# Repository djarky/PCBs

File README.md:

# PCBs
Various PCBs

- game controller based on digispark
- clap switch with relay
- amps?
- others

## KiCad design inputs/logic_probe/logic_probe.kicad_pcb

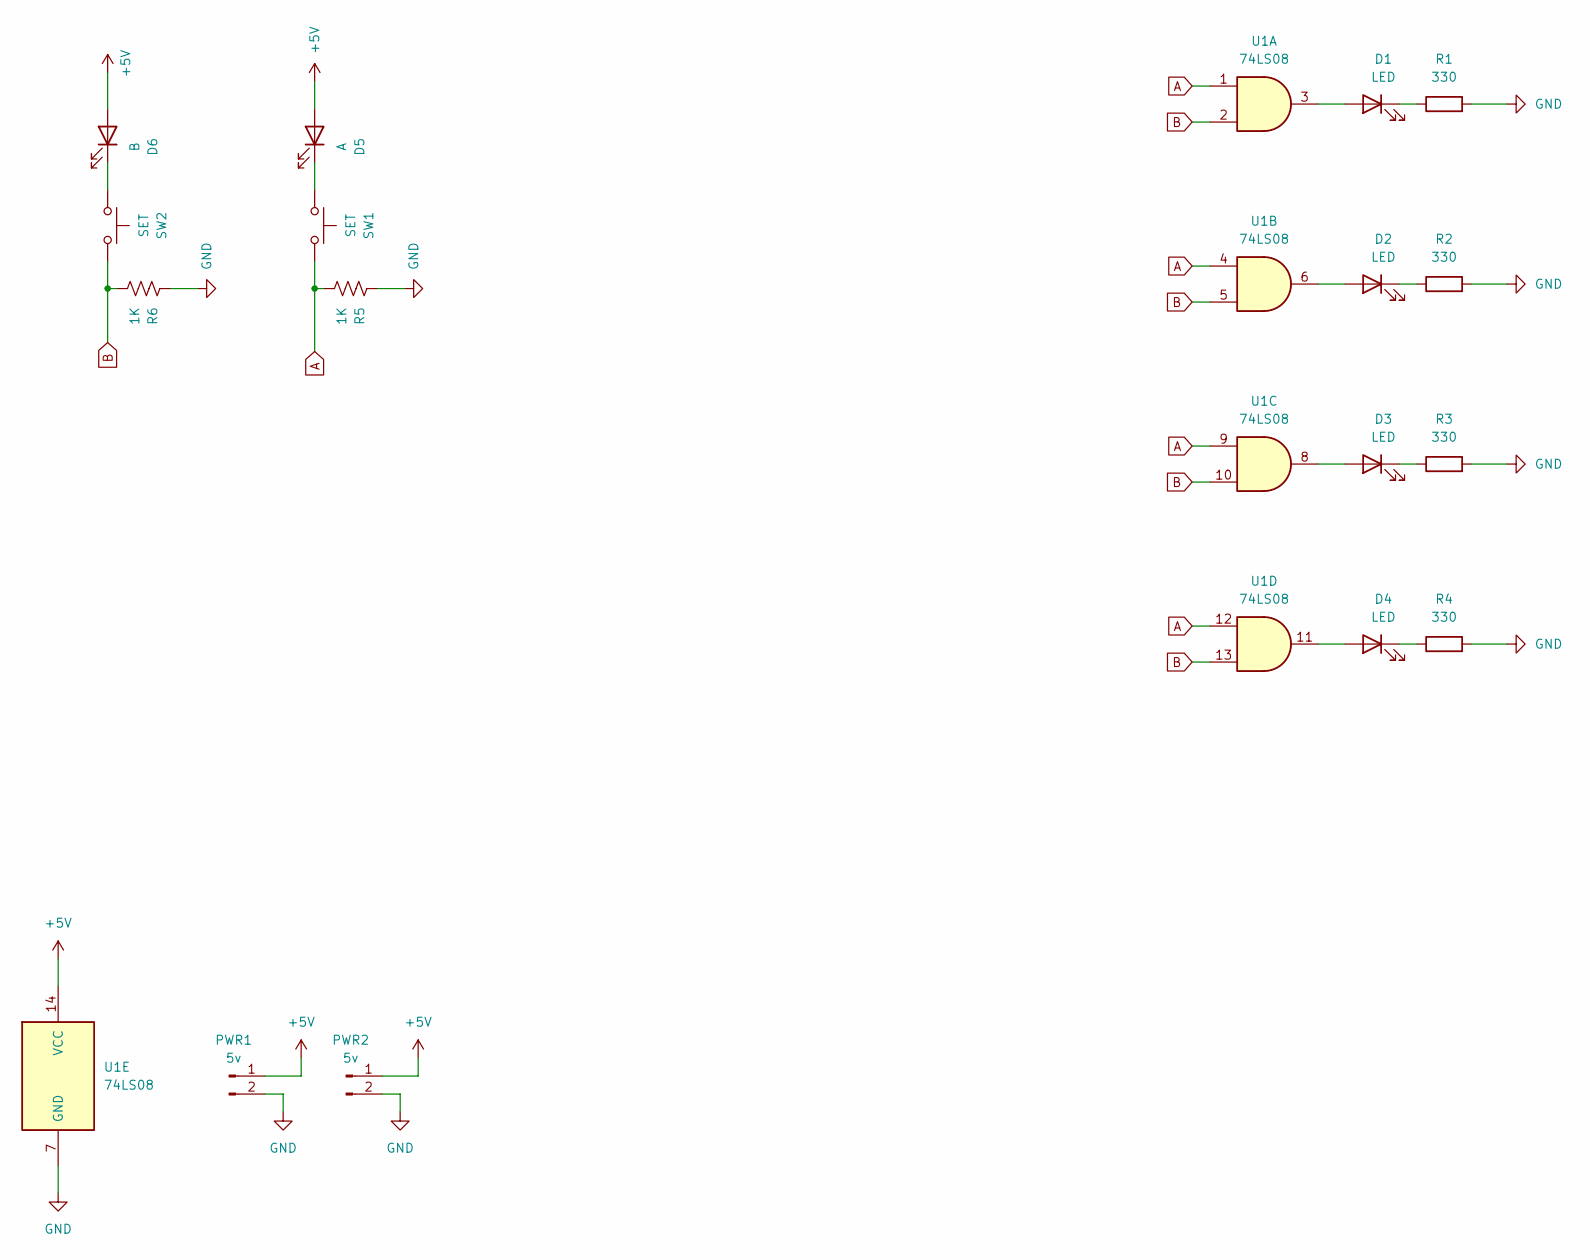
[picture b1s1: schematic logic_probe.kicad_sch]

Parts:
D1, D2, D3, D4: LED; LED_D4.0mm
D5: A; LED_D4.0mm
D6: B; LED_D4.0mm
PWR1, PWR2: 5v; PinSocket_1x02_P2.54mm_Vertical
R1, R2, R3, R4: 330; R_Axial_DIN0309_L9.0mm_D3.2mm_P12.70mm_Horizontal
R5, R6: 1K; R_Axial_DIN0309_L9.0mm_D3.2mm_P12.70mm_Horizontal
SW1, SW2: SET; SW_PUSH-12mm_Wuerth-430476085716
U1: 74LS08; DIP-14_W7.62mm_Socket_LongPads

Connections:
+5V: D5.2 (A), D6.2 (A), PWR1.1, PWR2.1, U1.14 (VCC)
A: R5.2, SW1.2, U1.1, U1.4, U1.9, U1.12
B: R6.2, SW2.2, U1.2, U1.5, U1.10, U1.13
GND: PWR1.2, PWR2.2, R1.2, R2.2, R3.2, R4.2, R5.1, R6.1, U1.7 (GND)
unnamed: D1.2 (A), U1.3
unnamed: D1.1 (K), R1.1
unnamed: D2.2 (A), U1.6
unnamed: D2.1 (K), R2.1
unnamed: D3.2 (A), U1.8
unnamed: D3.1 (K), R3.1
unnamed: D4.2 (A), U1.11
unnamed: D4.1 (K), R4.1
unnamed: D5.1 (K), SW1.1
unnamed: D6.1 (K), SW2.1

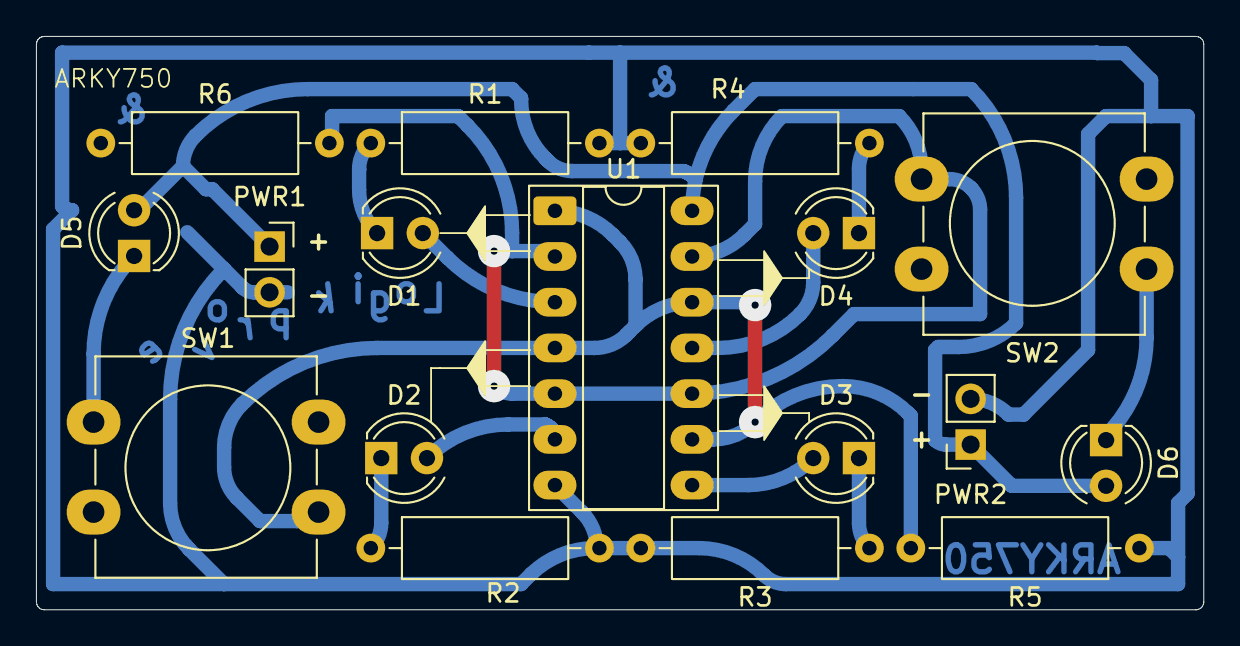
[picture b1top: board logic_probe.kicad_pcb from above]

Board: 2 copper layers, 64.8 x 31.8 mm, 17 parts (0 on the bottom side), 14 nets.

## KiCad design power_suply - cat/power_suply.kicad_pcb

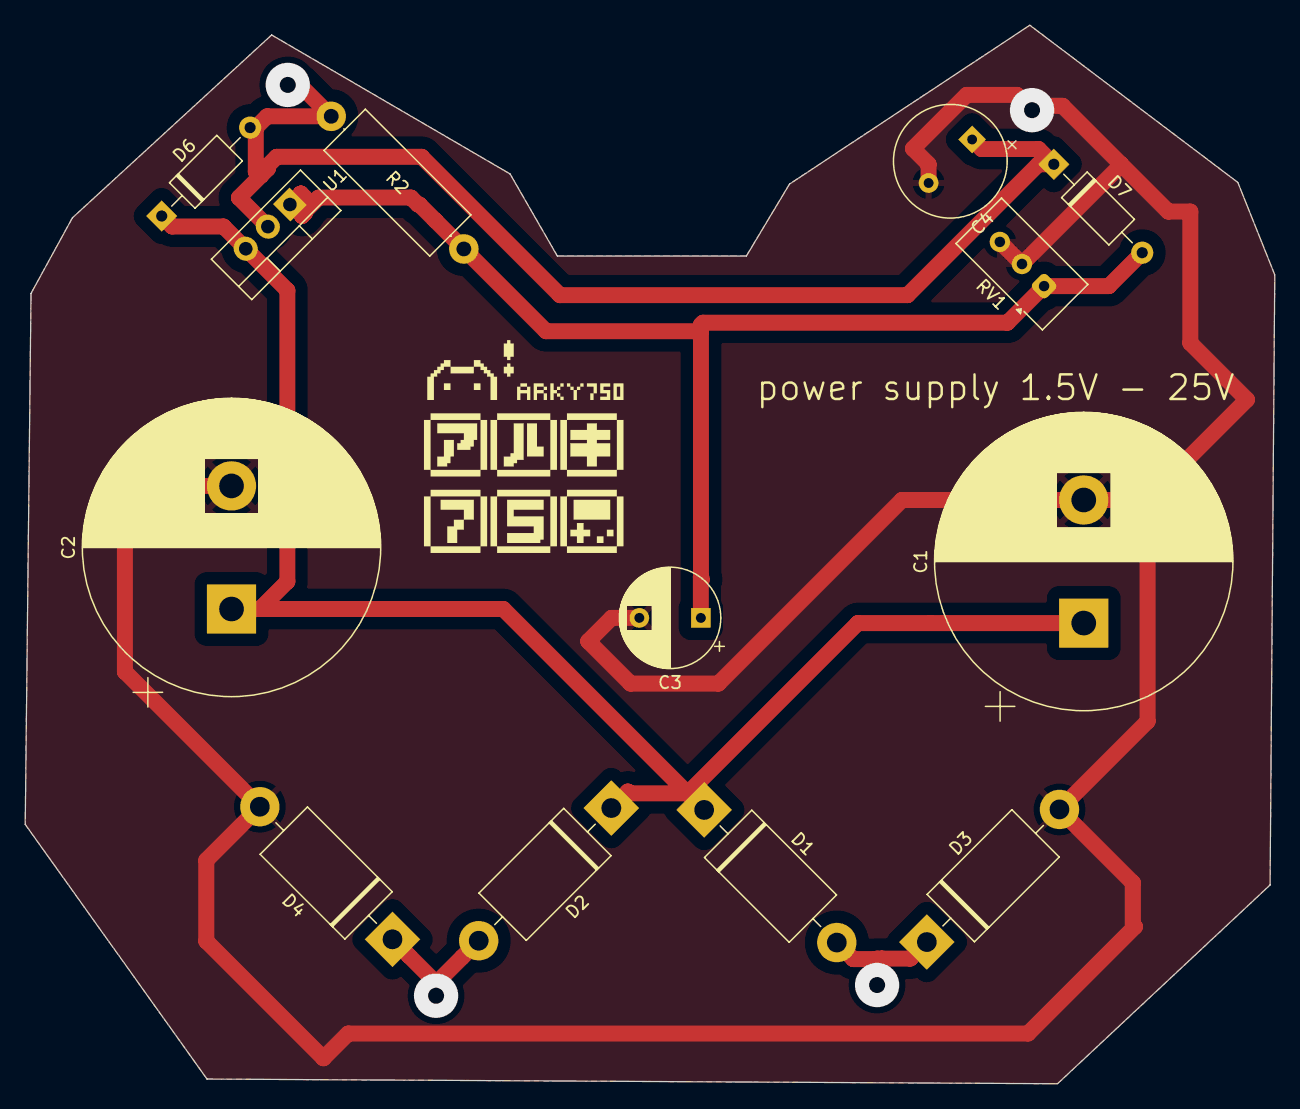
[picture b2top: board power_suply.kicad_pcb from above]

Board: 2 copper layers, 101.5 x 86.0 mm, 13 parts (0 on the bottom side), 6 nets.

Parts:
C1, C2: 2200uF 50v; CP_Radial_D24.0mm_P10.00mm_SnapIn
C3: 33uF 10V; CP_Radial_D8.0mm_P5.00mm
C4: 1uF 25V tantalio; CP_Radial_Tantal_D9.0mm_P5.00mm
D1, D2, D3, D4: D_Filled; D_DO-201AD_P15.24mm_Horizontal
D6: D_Filled; D_A-405_P10.16mm_Horizontal
D7: 1N4004; D_A-405_P10.16mm_Horizontal
R2: 240; R_Axial_DIN0414_L11.9mm_D4.5mm_P15.24mm_Horizontal
RV1: 5K; Potentiometer_Vishay_T93YA_Vertical
U1: LM317_TO-220; TO-220-3_Vertical

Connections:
GND: C1.2, C2.2, C3.2, C4.2, D3.2 (A), D4.2 (A), RV1.2, RV1.3
unnamed: D2.2 (A), D4.1 (K)
unnamed: C3.1, D7.2 (A), R2.2, RV1.1, U1.1 (ADJ)
T1: D1.2 (A), D3.1 (K)
Vin: C1.1, C2.1, D1.1 (K), D2.1 (K), D6.1 (K), U1.3 (VI)
Vout: C4.1, D6.2 (A), D7.1 (K), R2.1, U1.2 (VO)

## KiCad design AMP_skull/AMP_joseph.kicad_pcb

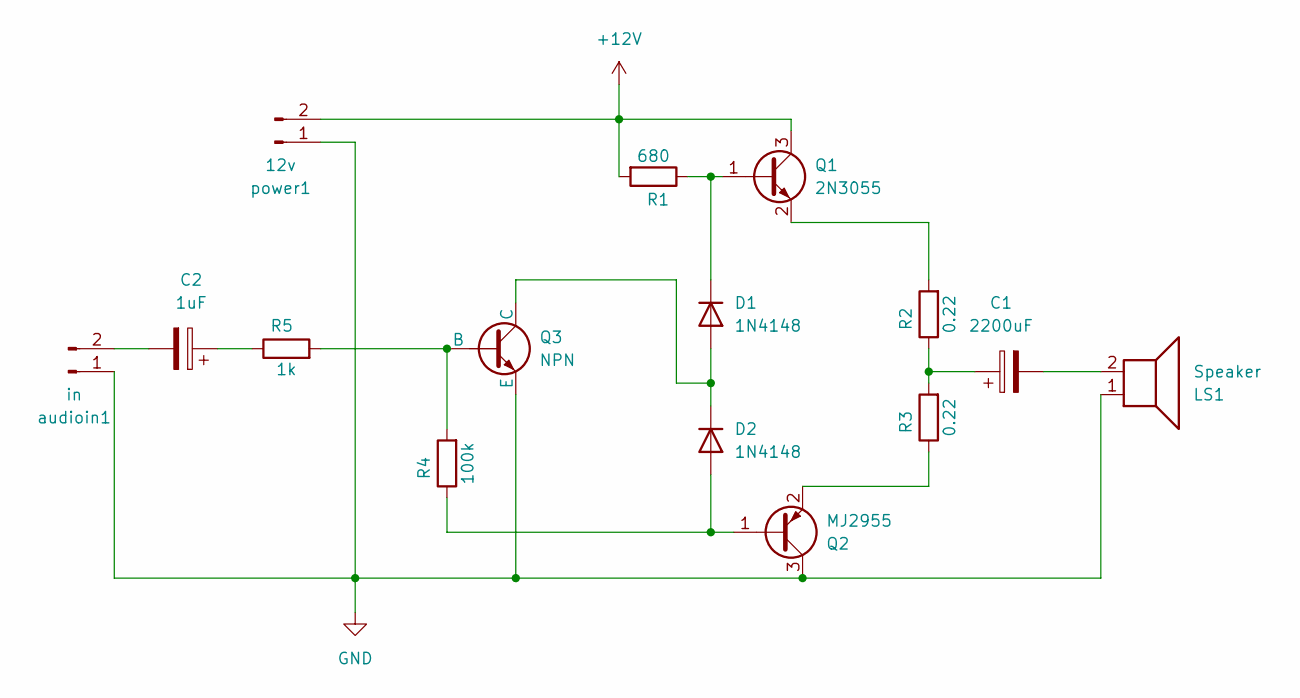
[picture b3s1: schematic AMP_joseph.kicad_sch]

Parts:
C1: 2200uF; CP_Radial_D10.0mm_P7.50mm
C2: 1uF; CP_Radial_D8.0mm_P5.00mm
D1, D2: 1N4148; D_DO-35_SOD27_P7.62mm_Horizontal
LS1: Speaker; TerminalBlock_Phoenix_MKDS-1,5-2-5.08_1x02_P5.08mm_Horizont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
Q1: 2N3055; TO-3
Q2: MJ2955; TO-3
Q3: NPN; TO-92L_Wide
R1: 680; R_Axial_DIN0414_L11.9mm_D4.5mm_P15.24mm_Horizontal
R2, R3: 0.22; R_Axial_DIN0516_L15.5mm_D5.0mm_P25.40mm_Horizontal
R4: 100k; R_Axial_DIN0414_L11.9mm_D4.5mm_P15.24mm_Horizontal
R5: 1k; R_Axial_DIN0414_L11.9mm_D4.5mm_P15.24mm_Horizontal
audioin1: in; TerminalBlock_Phoenix_MKDS-1,5-2-5.08_1x02_P5.08mm_Horizont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
power1: 12v; TerminalBlock_Phoenix_MKDS-1,5-2-5.08_1x02_P5.08mm_Horizont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

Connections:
+12V: Q1.3 (C), R1.2, power1.2
GND: LS1.1, Q2.3 (C), Q3.3 (E), audioin1.1, power1.1
unnamed: C1.1, R2.1, R3.2
unnamed: C1.2, LS1.2
unnamed: C2.1, R5.1
unnamed: D1.2 (A), D2.1 (K), Q3.1 (C)
unnamed: D1.1 (K), Q1.1 (B), R1.1
unnamed: D2.2 (A), Q2.1 (B), R4.1
unnamed: Q1.2 (E), R2.2
unnamed: Q2.2 (E), R3.1
unnamed: Q3.2 (B), R4.2, R5.2
unnamed: C2.2, audioin1.2

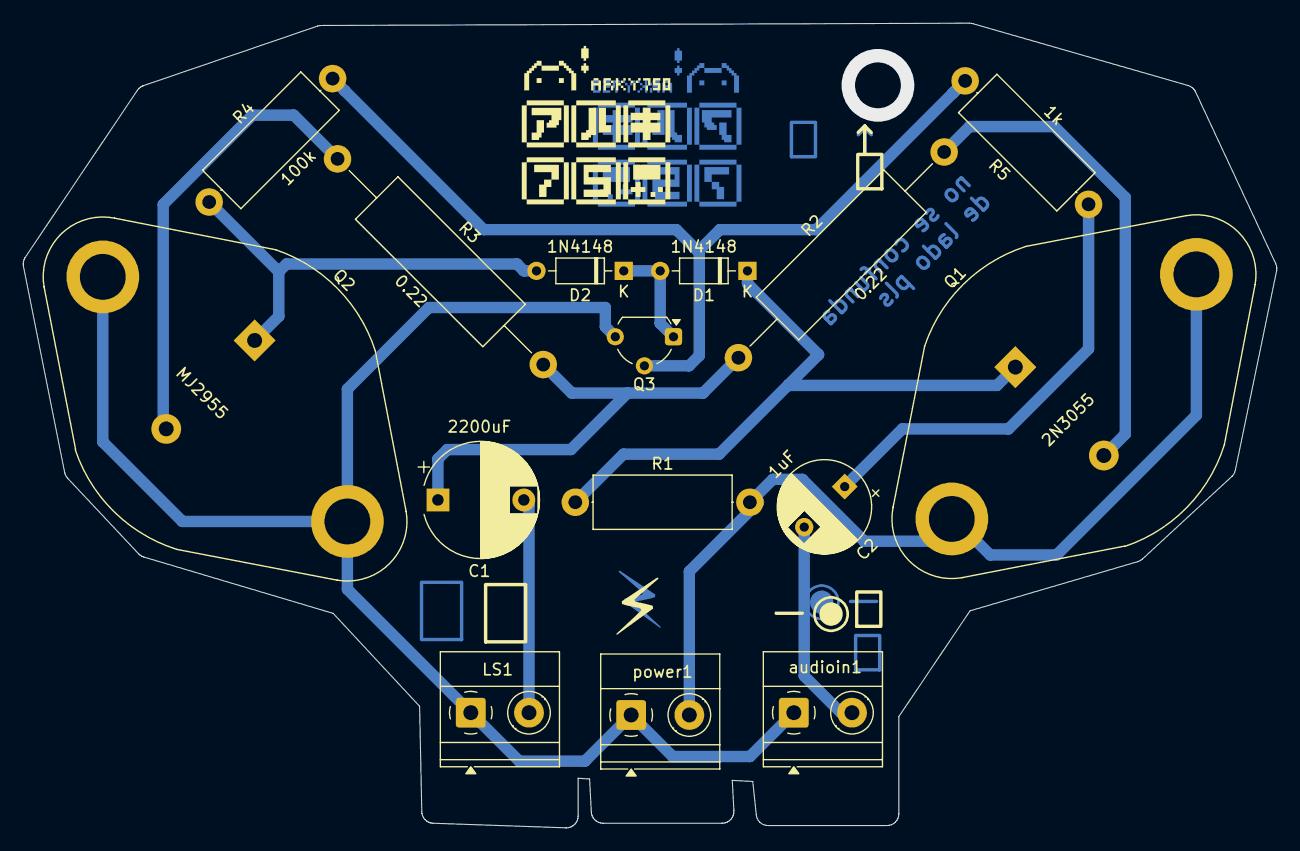
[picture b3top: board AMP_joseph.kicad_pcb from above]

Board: 2 copper layers, 109.4 x 70.2 mm, 15 parts (0 on the bottom side), 12 nets.

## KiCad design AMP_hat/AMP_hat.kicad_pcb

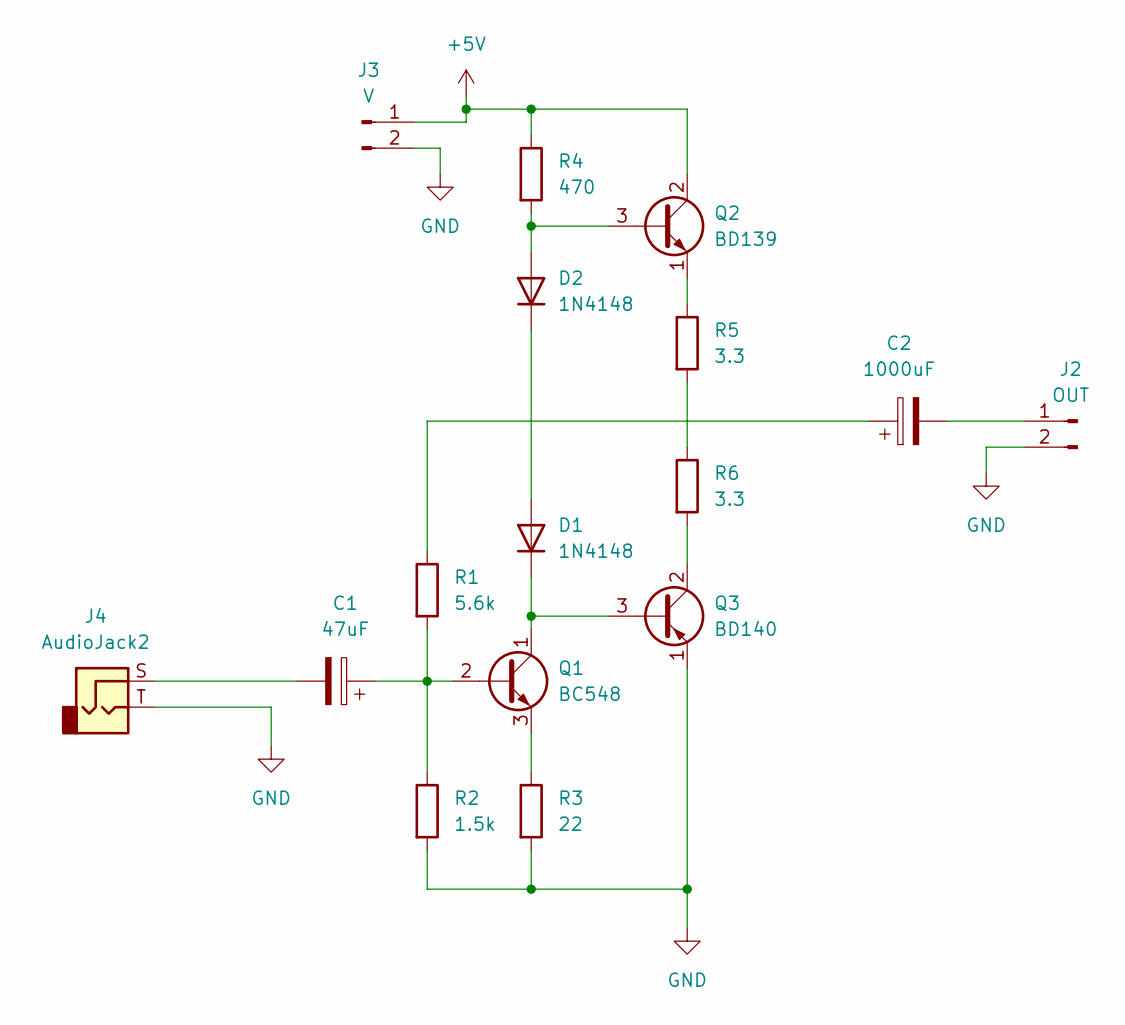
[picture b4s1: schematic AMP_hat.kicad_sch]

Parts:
C1: 47uF; CP_Radial_D4.0mm_P2.00mm
C2: 1000uF; CP_Radial_D10.0mm_P7.50mm
D1, D2: 1N4148; D_DO-35_SOD27_P7.62mm_Horizontal
J2: OUT; TerminalBlock_Phoenix_MKDS-1,5-2-5.08_1x02_P5.08mm_Horizont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
J3: V; TerminalBlock_Phoenix_MKDS-1,5-2-5.08_1x02_P5.08mm_Horizont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
J4: AudioJack2; Jack_3.5mm_CUI_SJ-3523-SMT_Horizontal
Q1: BC548; TO-92_Inline
Q2: BD139; TO-126-3_Vertical
Q3: BD140; TO-126-3_Vertical
R1: 5.6k; R_Axial_DIN0309_L9.0mm_D3.2mm_P12.70mm_Horizontal
R2: 1.5k; R_Axial_DIN0309_L9.0mm_D3.2mm_P12.70mm_Horizontal
R3: 22; R_Axial_DIN0309_L9.0mm_D3.2mm_P12.70mm_Horizontal
R4: 470; R_Axial_DIN0309_L9.0mm_D3.2mm_P12.70mm_Horizontal
R5, R6: 3.3; R_Axial_DIN0309_L9.0mm_D3.2mm_P12.70mm_Horizontal

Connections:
+5V: J3.1, Q2.2 (C), R4.1
GND: J2.2, J3.2, J4.T, Q3.1 (E), R2.2, R3.2
unnamed: C1.2, J4.S
unnamed: C2.1, R1.1
unnamed: D1.2 (A), D2.1 (K)
unnamed: D1.1 (K), Q1.1 (C), Q3.3 (B)
unnamed: D2.2 (A), Q2.3 (B), R4.2
unnamed: C2.2, J2.1
unnamed: C1.1, Q1.2 (B), R1.2, R2.1
unnamed: Q1.3 (E), R3.1
unnamed: Q2.1 (E), R5.1
unnamed: Q3.2 (C), R6.2
unnamed: R5.2, R6.1

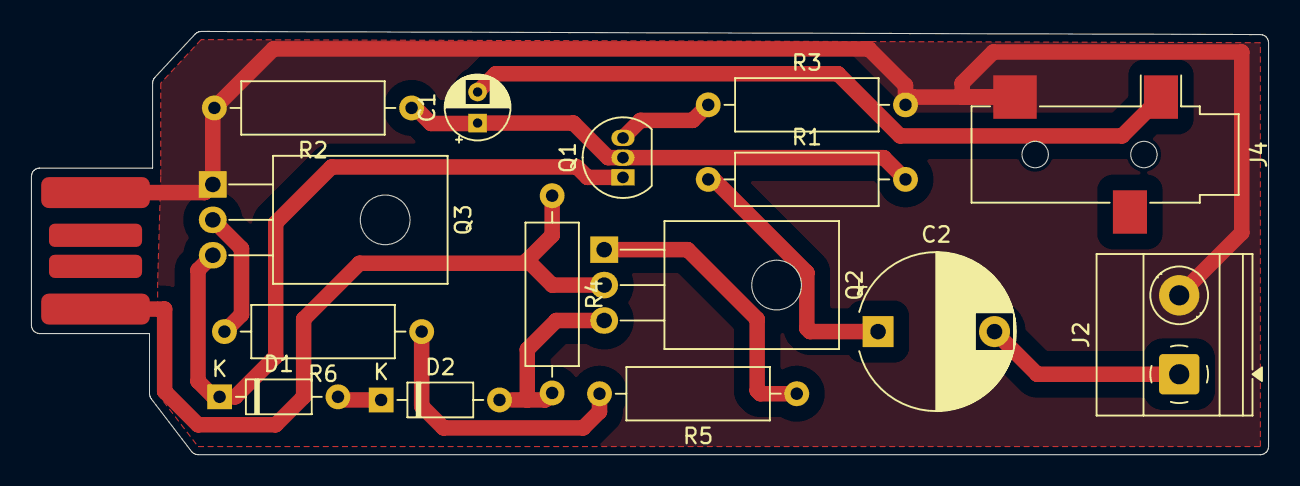
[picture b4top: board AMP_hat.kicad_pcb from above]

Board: 2 copper layers, 79.7 x 27.2 mm, 15 parts (0 on the bottom side), 13 nets.

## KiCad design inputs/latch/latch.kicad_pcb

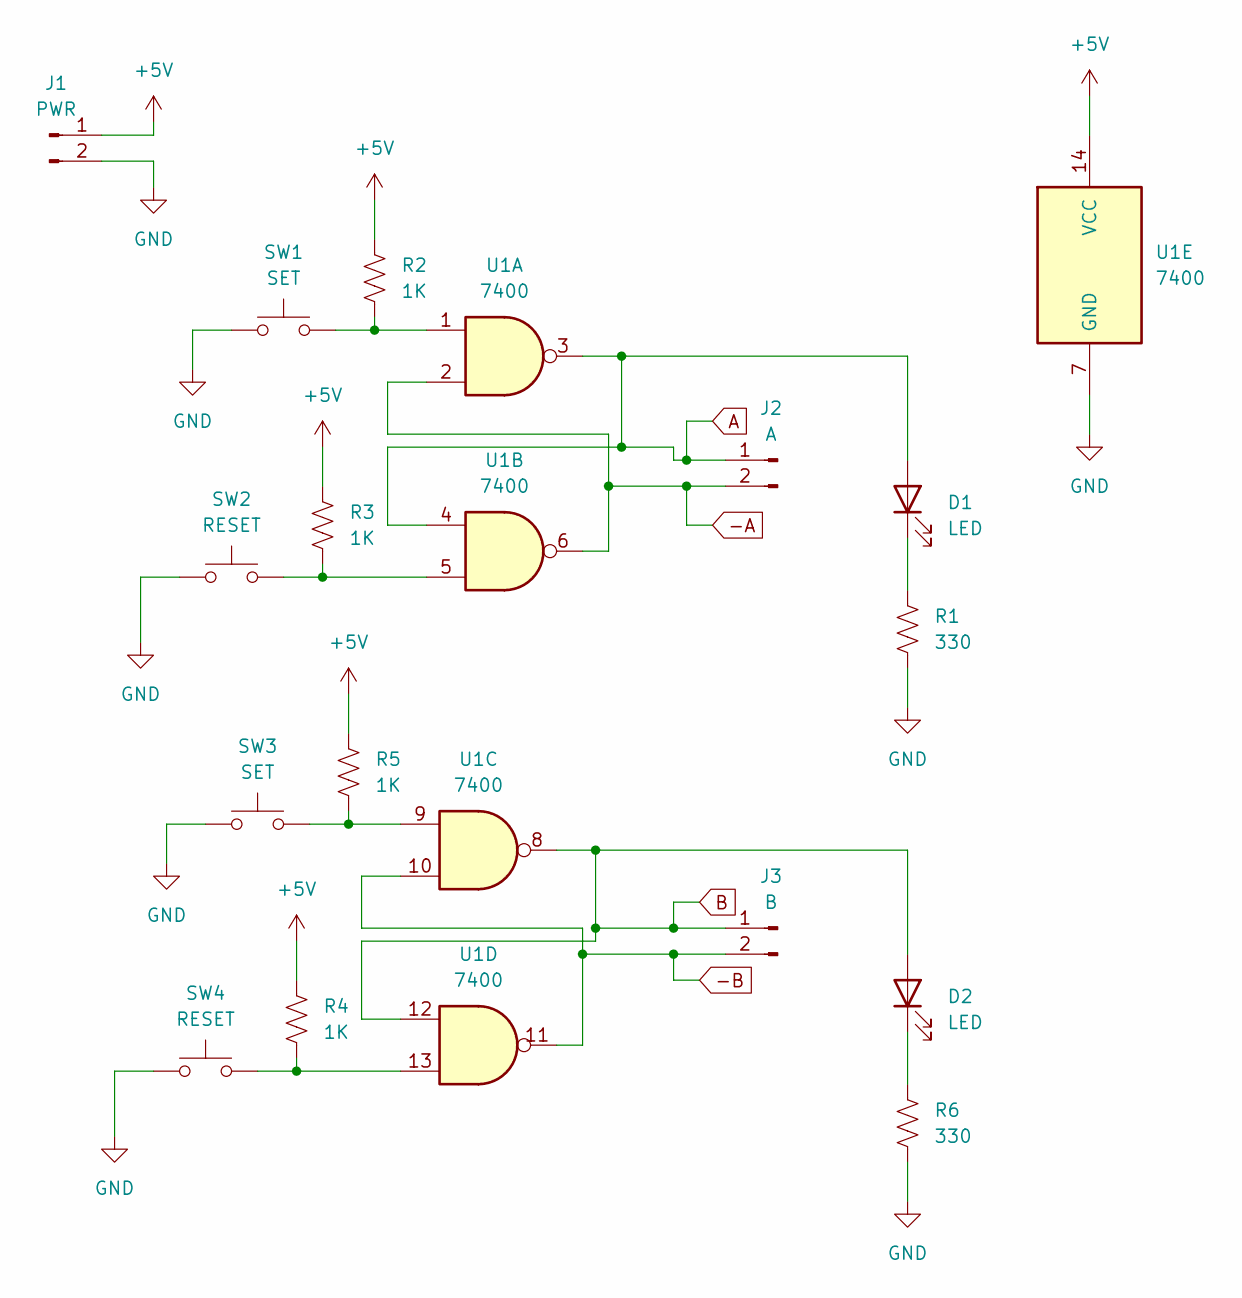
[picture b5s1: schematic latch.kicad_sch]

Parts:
D1, D2: LED; LED_D4.0mm
J1: PWR; PinHeader_2x01_P2.54mm_Vertical
J2: A; PinHeader_2x01_P2.54mm_Vertical
J3: B; PinHeader_2x01_P2.54mm_Vertical
R1, R6: 330; R_Axial_DIN0414_L11.9mm_D4.5mm_P20.32mm_Horizontal
R2, R3, R4, R5: 1K; R_Axial_DIN0414_L11.9mm_D4.5mm_P20.32mm_Horizontal
SW1, SW3: SET; SW_PUSH-12mm_Wuerth-430476085716
SW2, SW4: RESET; SW_PUSH-12mm_Wuerth-430476085716
U1: 7400; DIP-14_W10.16mm_LongPads

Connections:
+5V: J1.1, R2.1, R3.1, R4.1, R5.1, U1.14 (VCC)
-A: J2.2, U1.2, U1.6
-B: J3.2, U1.10, U1.11
A: D1.2 (A), J2.1, U1.3, U1.4
B: D2.2 (A), J3.1, U1.8, U1.12
GND: J1.2, R1.2, R6.2, SW1.1, SW2.1, SW3.1, SW4.1, U1.7 (GND); also elsewhere on the board
unnamed: D1.1 (K), R1.1
unnamed: D2.1 (K), R6.1
unnamed: R2.2, SW1.2, U1.1
unnamed: R3.2, SW2.2, U1.5
unnamed: R4.2, SW4.2, U1.13
unnamed: R5.2, SW3.2, U1.9

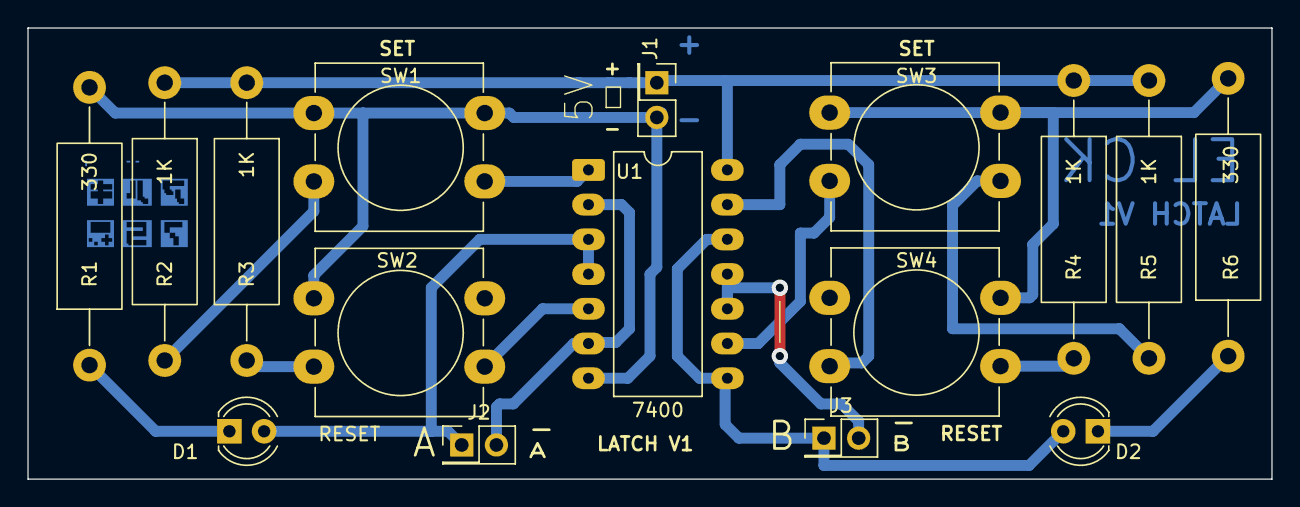
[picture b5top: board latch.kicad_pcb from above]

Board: 2 copper layers, 91.0 x 33.0 mm, 17 parts (1 on the bottom side), 12 nets.

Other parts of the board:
logo_arky: LOGO

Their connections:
GND: logo_arky.1; also elsewhere on the board

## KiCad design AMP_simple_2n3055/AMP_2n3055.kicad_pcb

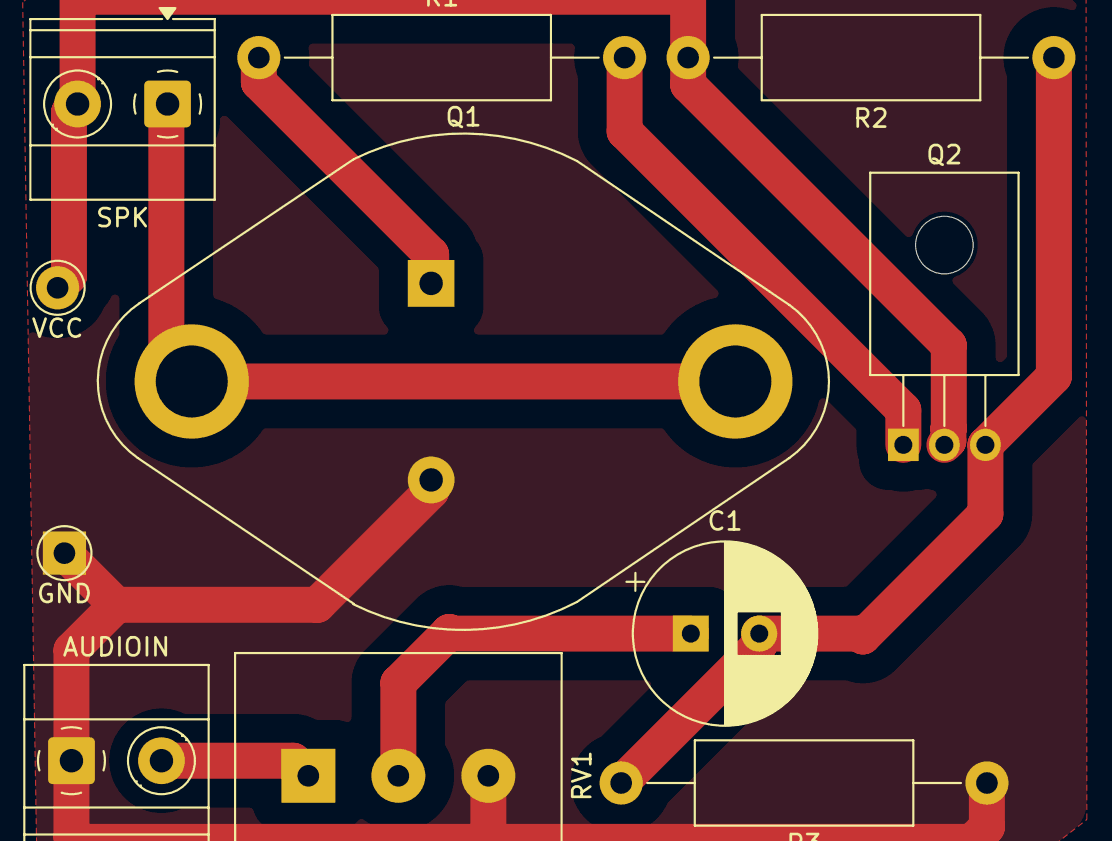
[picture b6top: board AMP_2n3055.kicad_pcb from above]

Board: 2 copper layers, 11 parts (0 on the bottom side), 8 nets.

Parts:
AUDIOIN: IN; TerminalBlock_Phoenix_MKDS-1,5-2_1x02_P5.00mm_Horizontal
C1: 10uF; CP_Radial_D10.0mm_P3.80mm
GND: GND; Pin_D1.0mm_L10.0mm_LooseFit
Q1: 2N3055; TO-3
Q2: BD139; TO-126-3_Horizontal_TabDown
R1: 82; R_Axial_DIN0414_L11.9mm_D4.5mm_P20.32mm_Horizontal
R2: 100K; R_Axial_DIN0414_L11.9mm_D4.5mm_P20.32mm_Horizontal
R3: 47K; R_Axial_DIN0414_L11.9mm_D4.5mm_P20.32mm_Horizontal
RV1: 50K; Potentiometer_Alps_RK163_Single_Horizontal
SPK: SPK; TerminalBlock_Phoenix_MKDS-1,5-2_1x02_P5.00mm_Horizontal
VCC: 12V; Pin_D1.0mm_L10.0mm_LooseFit

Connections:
GND: AUDIOIN.1, GND.1, Q1.2 (E), R3.1, RV1.3
IN: AUDIOIN.2, RV1.1
unnamed: C1.1, RV1.2
unnamed: Q1.1 (B), R1.1
unnamed: C1.2, Q2.3 (B), R2.1, R3.2
unnamed: Q2.1 (E), R1.2
P+: Q2.2 (C), R2.2, SPK.2, VCC.1
P-: Q1.3 (C), SPK.1

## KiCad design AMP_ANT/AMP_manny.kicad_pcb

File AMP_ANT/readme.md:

IMPORTANT NOTE:

This motherboard is poorly designed because the class AB configuration is not properly balanced.

The design was taken from this page: [https://amplificadoresaudio.blogspot.com/2012/06/amplificador-transistorizado-de-
90-w.html](https://amplificadoresaudio.blogspot.com/2012/06/amplificador-transistorizado-de-90-w.html)

If you're interested in the motherboard, you could improve it by researching and using the correct configuration, and if you do, please let me know.

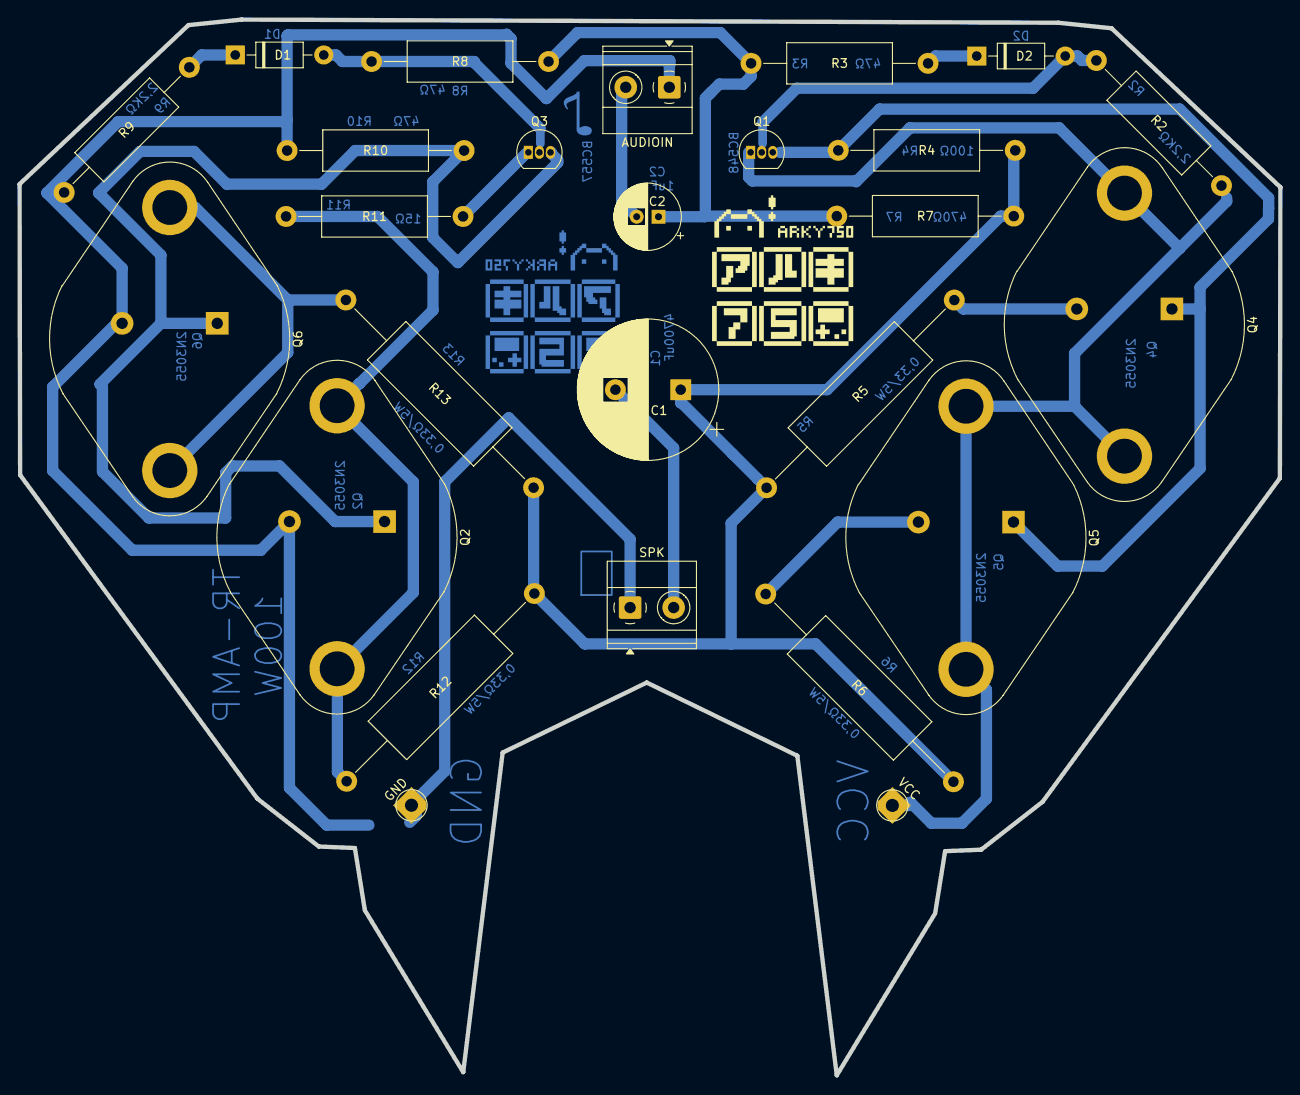
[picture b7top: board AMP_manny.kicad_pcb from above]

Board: 2 copper layers, 144.8 x 121.2 mm, 26 parts (0 on the bottom side), 17 nets.

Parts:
AUDIOIN: AudioJack2; TerminalBlock_Phoenix_MKDS-1,5-2_1x02_P5.00mm_Horizontal
C1: 4700uF; CP_Radial_D16.0mm_P7.50mm
C2: 1uF; CP_Radial_D7.5mm_P2.50mm
D1, D2: 1N4001; D_DO-41_SOD81_P10.16mm_Horizontal
GND: GND; Pin_D1.3mm_L11.0mm_LooseFit
Q1: BC548; TO-92_Inline
Q2, Q4, Q5, Q6: 2N3055; TO-3
Q3: BC557; TO-92_Inline
R2, R9: 2,2KΩ; R_Axial_DIN0414_L11.9mm_D4.5mm_P20.32mm_Horizontal
R3, R8, R10: 47Ω; R_Axial_DIN0414_L11.9mm_D4.5mm_P20.32mm_Horizontal
R4: 100Ω; R_Axial_DIN0414_L11.9mm_D4.5mm_P20.32mm_Horizontal
R5: 0,33/5W; R_Axial_DIN0617_L17.0mm_D6.0mm_P30.48mm_Horizontal
R6, R12, R13: 0,33Ω/5W; R_Axial_DIN0617_L17.0mm_D6.0mm_P30.48mm_Horizontal
R7: 470Ω; R_Axial_DIN0414_L11.9mm_D4.5mm_P20.32mm_Horizontal
R11: 15Ω; R_Axial_DIN0414_L11.9mm_D4.5mm_P20.32mm_Horizontal
SPK: Speaker; TerminalBlock_Phoenix_MKDS-1,5-2_1x02_P5.00mm_Horizontal
VCC: VCC; Pin_D1.3mm_L11.0mm_LooseFit

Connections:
GND: AUDIOIN.1, GND.1, Q2.2 (E), Q6.2 (E), R9.2, R10.2, SPK.1
IN: AUDIOIN.2, C2.2
unnamed: C1.1, R4.2, R5.2, R6.2, R7.2, R12.1, R13.1
unnamed: C1.2, SPK.2
unnamed: C2.1, R3.2, R7.1, R8.1
unnamed: D1.2 (A), Q3.2 (B), R8.2
unnamed: D1.1 (K), R9.1
unnamed: D2.2 (A), Q1.2 (B), R2.1
unnamed: D2.1 (K), R3.1
unnamed: Q1.3 (E), Q4.1 (B), Q5.1 (B), R4.1
unnamed: Q2.1 (B), Q3.3 (E), Q6.1 (B), R10.1
unnamed: Q2.3 (C), R11.2, R12.2
unnamed: Q3.1 (C), R11.1
unnamed: Q4.2 (E), R5.1
unnamed: Q5.2 (E), R6.1
unnamed: Q6.3 (C), R13.2
VCC: Q1.1 (C), Q4.3 (C), Q5.3 (C), R2.2, VCC.1

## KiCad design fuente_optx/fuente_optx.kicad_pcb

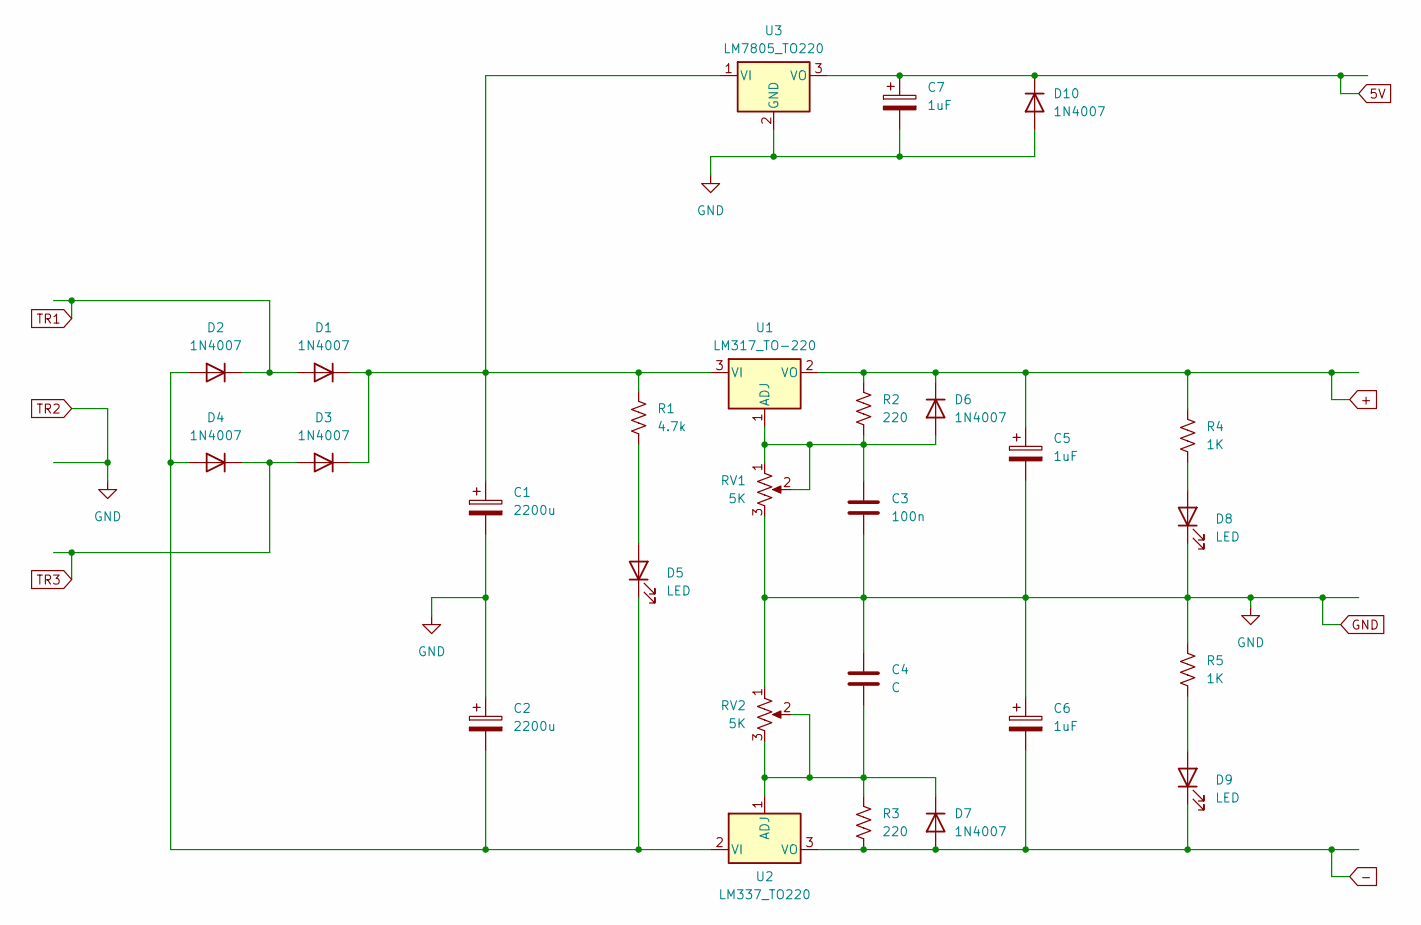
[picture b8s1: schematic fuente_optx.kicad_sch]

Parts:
C1, C2: 2200u; CP_Radial_D25.0mm_P10.00mm_SnapIn
C3: 100n; C_Disc_D14.5mm_W5.0mm_P10.00mm
C4: C; C_Disc_D14.5mm_W5.0mm_P10.00mm
C5, C6, C7: 1uF; CP_Radial_D14.0mm_P7.50mm
D1, D2, D3, D4, D6, D7, D10: 1N4007; D_DO-41_SOD81_P10.16mm_Horizontal
D5, D8, D9: LED; LED_D5.0mm
R1: 4.7k; R_Axial_DIN0414_L11.9mm_D4.5mm_P20.32mm_Horizontal
R2, R3: 220; R_Axial_DIN0414_L11.9mm_D4.5mm_P20.32mm_Horizontal
R4, R5: 1K; R_Axial_DIN0414_L11.9mm_D4.5mm_P20.32mm_Horizontal
RV1, RV2: 5K; Potentiometer_Vishay_T93YA_Vertical
U1: LM317_TO-220; TO-220-3_Vertical
U2: LM337_TO220; TO-220-3_Vertical
U3: LM7805_TO220; TO-220-3_Vertical

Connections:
5V: C7.1, D10.1 (K), U3.3 (VO)
+: C5.1, D6.1 (K), R2.1, R4.1, U1.2 (VO)
-: C6.2, D7.2 (A), D9.1 (K), R3.2, U2.3 (VO)
GND: C1.2, C2.1, C3.2, C4.1, C5.2, C6.1, C7.2, D8.1 (K), D10.2 (A), R5.1, RV1.3, RV2.1, U3.2 (GND)
unnamed: C1.1, D1.1 (K), D3.1 (K), R1.1, U1.3 (VI), U3.1 (VI)
unnamed: C2.2, D2.2 (A), D4.2 (A), D5.1 (K), U2.2 (VI)
unnamed: D5.2 (A), R1.2
unnamed: C3.1, D6.2 (A), R2.2, RV1.1, RV1.2, U1.1 (ADJ)
unnamed: C4.2, D7.1 (K), R3.1, RV2.2, RV2.3, U2.1 (ADJ)
unnamed: D8.2 (A), R4.2
unnamed: D9.2 (A), R5.2
TR1: D1.2 (A), D2.1 (K)
TR3: D3.2 (A), D4.1 (K)

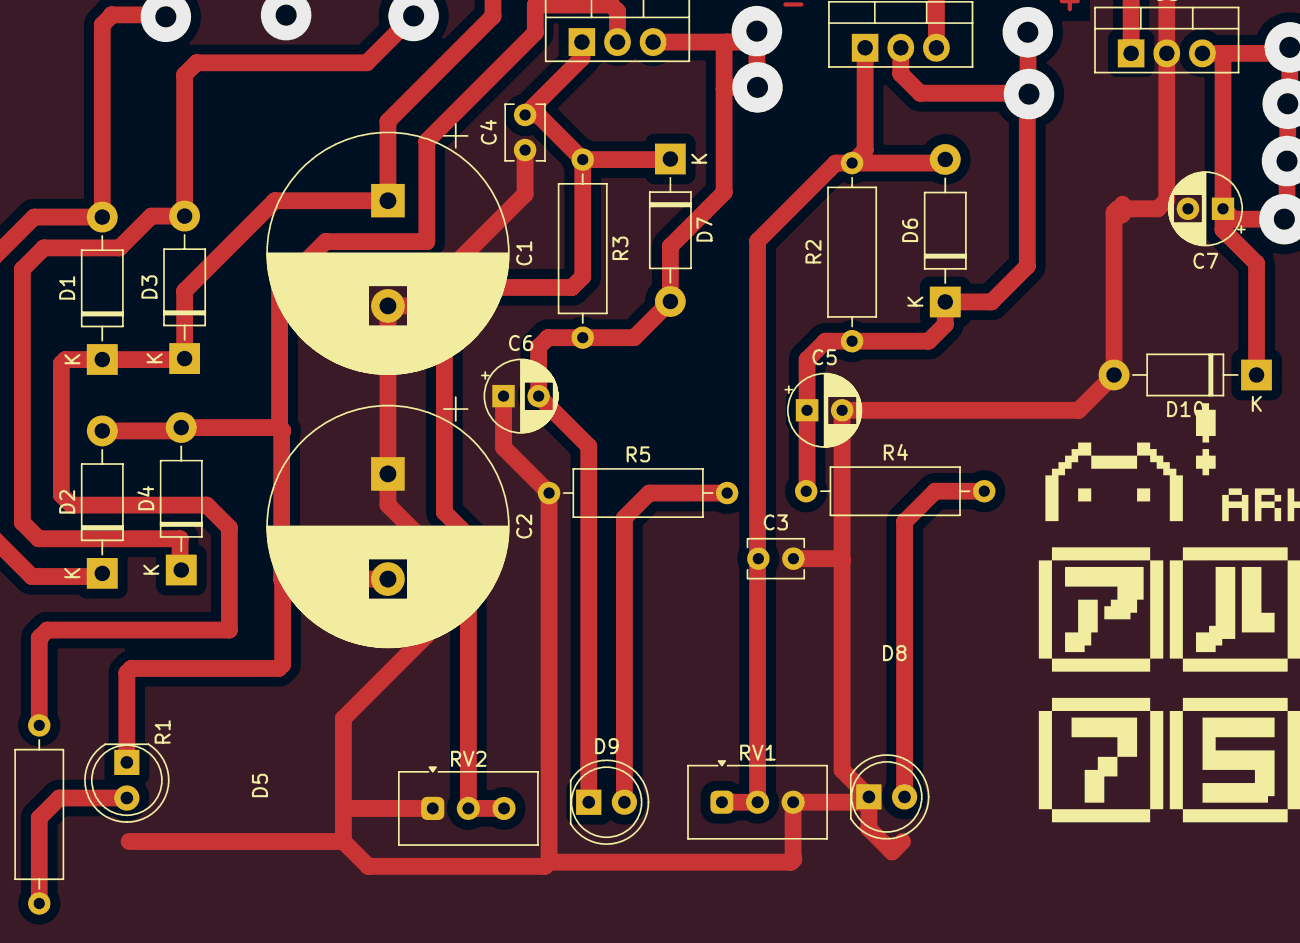
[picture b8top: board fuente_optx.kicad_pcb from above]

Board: 2 copper layers, 27 parts (0 on the bottom side), 13 nets.

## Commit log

2026-03-16 upgrade cat
